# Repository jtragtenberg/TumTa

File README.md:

# TumTa - Instrumento Digital de Dança e Música voltado a disparar samples sonoros a partir de pisadas através de uma palmilha sensível à pressão (FSR).

## Descrição

**TumTa** é um sistema híbrido, modular e open-source, que integra:

- Hardware de detecção percussiva sensível ao toque.
- Firmware embarcado com processamento em tempo real.
- Comunicação sem fio via **XBee**.
- Software receptor/visualizador desenvolvido em **C++ com OpenFrameworks**.

O sistema foi desenvolvido para aplicações em:

- Performance musical ao vivo.
- Instalações audiovisuais interativas.
- Pesquisas em interfaces físico-digitais.

## Componentes do Projeto

### 1. Circuito eletrônico

- Projeto de circuito com sensores piezoelétricos.
- Arquivos disponíveis no repositório:
  - Esquema elétrico (.sch).
  - PCB para fabricação ou CNC (.brd).
  - Layout da caixa para **corte a laser** (.svg ou .dxf).

Todos os arquivos estão na pasta `hardware/`.

### 2. Firmware (Arduino)

- Processamento de sinais em tempo real com:
  - Derivada via diferenças finitas (float).
  - Controle **não bloqueante** com `millis()`.
  - Sistema de **debounce** ajustável.
  - Modos de envio: `DEBUG` e `LIVE`.

- Comunicação serial com módulo **XBee** para transmissão sem fio.
- Código modular e otimizado disponível na pasta `firmware/`.

### 3. Comunicação sem fio (XBee)

- Configuração clássica:
  - Transmissor: Arduino + XBee.
  - Receptor: XBee + computador.

- Baudrate: 38400.
- Comunicação robusta com protocolo de mensagem e **checksum**.

### 4. Software receptor (OpenFrameworks)

Desenvolvido em **C++ com OpenFrameworks**, o software realiza:

- Recepção e interpretação das mensagens enviadas via XBee.
- Detecção de picos ajustável, permitindo o controle da sensibilidade à intensidade.
- Mapeamento dinâmico: a intensidade controla diretamente a dinâmica dos samples gerados.
- Contorno de ruídos: filtros e thresholds ajustáveis para minimizar falsos disparos.
- Interface com `ofxGui` para ajuste em tempo real.
- Visualização gráfica dos dados recebidos.

**Integração MIDI**:

- O software converte os eventos de detecção percussiva em **mensagens MIDI**.
- Utiliza bibliotecas como `ofxMidi` para envio MIDI.
- As mensagens MIDI são enviadas em tempo real para uma **DAW** (ex.: **Ableton Live**, **Logic Pro**, **Reaper**).
- Cada batida detectada pode ser mapeada para **notas MIDI específicas**, disparando samples ou instrumentos virtuais.

## Fluxo geral do sistema

```
Sensor Piezo → Arduino → Processamento → XBee TX → ~~~ Wireless ~~~ → XBee RX → OpenFrameworks → MIDI OUT → DAW (Ableton Live)
```

## Arquivos incluídos no repositório

| Pasta            | Conteúdo                                                 |
|------------------|----------------------------------------------------------|
| `PCB/ Enclosure/ | Esquema, PCB (.brd/.sch), layout da caixa (.svg/.dxf).   |
| `Arduino/`       | Código Arduino (`TumTa.ino`).                            |
| `OpenFrameWorks/`| Projeto OpenFrameworks com envio MIDI.                   |
| `Imagens/`       | Fotos                                                    |
| `Max/`           | Software Aternativo                                      |

## Como montar o sistema

### 1. Hardware

- Construa o circuito com base no esquema elétrico.
- Corte a caixa com laser utilizando os arquivos vetoriais.
- Monte os componentes, conecte sensores, potenciômetro e switches.

### 2. Firmware

- Abra o `TumTa.ino` no Arduino IDE.
- Compile e envie para a placa Arduino.

### 3. Comunicação

- Configure os módulos **XBee**:
  - Mesma PAN ID.
  - Baudrate: 38400.
- Conecte o transmissor ao Arduino e o receptor ao computador.

### 4. Software

- Instale **OpenFrameworks** (versão 0.11 ou superior).
- Inclua `ofxMidi` para envio de mensagens MIDI.
- Abra o projeto `TumTa` na pasta `software/`.
- Ajuste:
  - Porta serial para XBee receptor.
  - Configurações MIDI (porta virtual ou física).
- Compile e execute.
- Configure a DAW (ex.: **Ableton Live**) para receber as mensagens MIDI provenientes do software.

## Parâmetros ajustáveis

| Parâmetro                | Local                            | Valor padrão |
|------------------------- |--------------------------------- |------------- |
| Threshold                | Potenciômetro (A7)               | Variável     |
| Debounce Time            | Estrutura `ChannelState`         | 150 ms       |
| Process Interval         | Global                           | 1 ms         |
| Tempo de Pisca (LED)     | Global                           | 500 ms       |
| Sensibilidade de Pico    | Interface do OpenFrameworks      | Ajustável    |
| Dinâmica de Sample/MIDI  | Mapeamento no software           | Ajustável    |
| Notas MIDI mapeadas      | Configuração no OpenFrameworks   | Ajustável    |

## Diferenciais do projeto

- Modular e expansível, com suporte para múltiplos sensores.
- Processamento híbrido, com divisão de carga entre hardware e software.
- Integração robusta com sistemas artísticos interativos e musicais.
- Arquivos completos: circuito, caixa e software.
- Envio de MIDI para **DAW** em tempo real.

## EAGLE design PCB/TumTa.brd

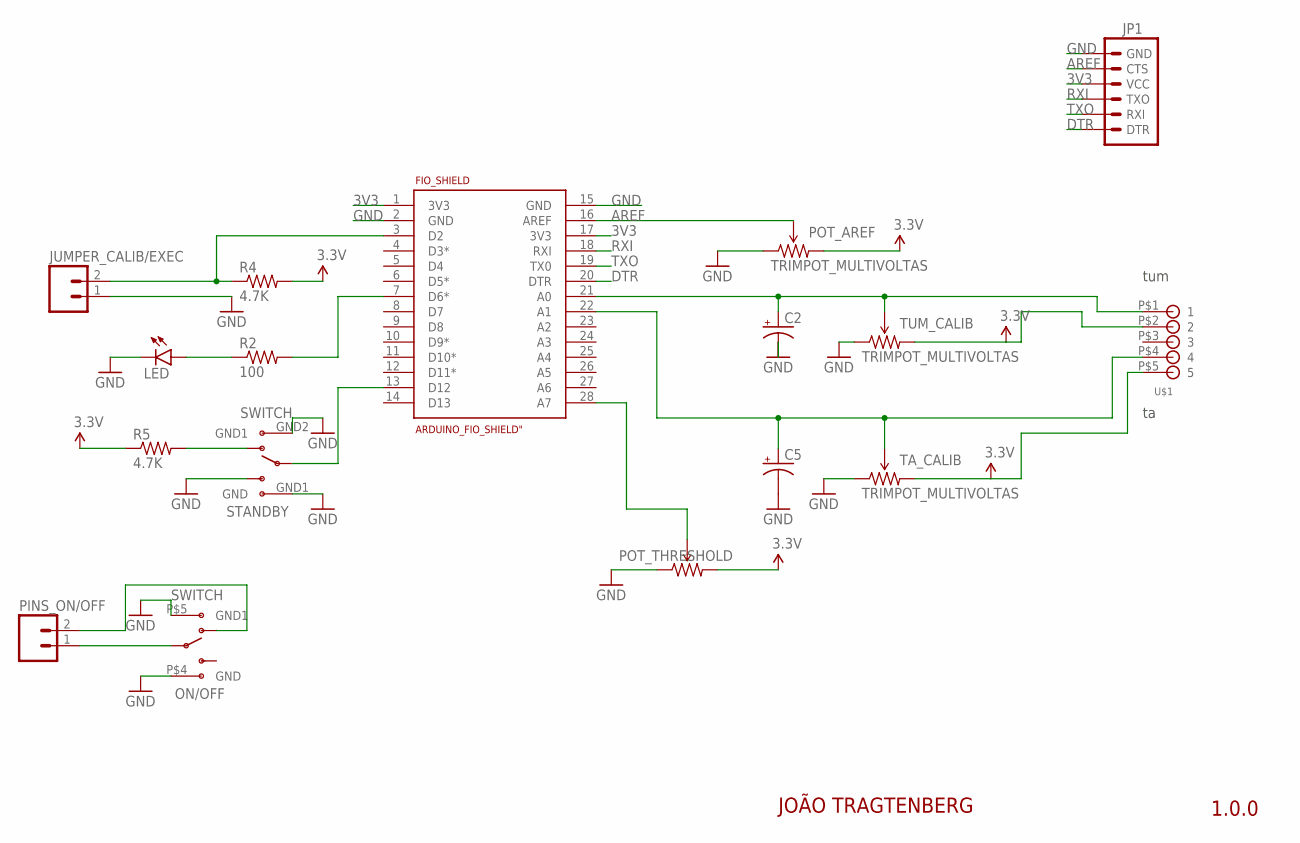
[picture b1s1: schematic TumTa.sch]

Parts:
C2, C5: CAP_POLPTH2; CPOL-RADIAL-10UF-25V
FIO_SHIELD: ARDUINO_FIO_SHIELD"; ARDUINO_FIO_SHIELD
JP1: ARDUINO_SERIAL_PROGRAMPTH; 1X06
JUMPER_CALIB/EXEC: M02PTH; 1X02
LED: LED-GREEN5MM_THRU; LED5MM
ON/OFF: SWITCH; SWITCH_HH_2POS_3PIN
PINS_ON/OFF: M02PTH; 1X02
POT_AREF: TRIMPOT_MULTIVOLTAS
POT_THRESHOLD: TRIMPOTBR; TRIM_POT_BR
R2: 100; 0603-RES
R4, R5: 4.7K; 0603-RES
STANDBY: SWITCH; SWITCH_HH_2POS_6PIN
TA_CALIB: TRIMPOT_MULTIVOLTAS
TUM_CALIB: TRIMPOT_MULTIVOLTAS
U$1: SCREWTERMINAL-5; SCREWTERMINAL-0.1"-5_BR

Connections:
3V3: FIO_SHIELD.1 (3V3), FIO_SHIELD.17 (3V3), JP1.4 (VCC), POT_AREF.3 (CW), POT_THRESHOLD.3 (CW), R4.2, R5.1, TA_CALIB.3 (CW), TUM_CALIB.3 (CW), U$1.P$2 (2), U$1.P$5 (5)
A0: C2.1 (+), FIO_SHIELD.21 (A0), TUM_CALIB.2 (WIPER), U$1.P$1 (1)
A1: C5.1 (+), FIO_SHIELD.22 (A1), TA_CALIB.2 (WIPER), U$1.P$4 (4)
AREF: FIO_SHIELD.16 (AREF), JP1.5 (CTS), POT_AREF.2 (WIPER)
D10: FIO_SHIELD.7 (D6*), R2.2
DTR: FIO_SHIELD.20 (DTR), JP1.1 (DTR)
GND: C2.2 (-), C5.2 (-), FIO_SHIELD.2 (GND), FIO_SHIELD.15 (GND), JP1.6 (GND), JUMPER_CALIB/EXEC.1, LED.K (C), ON/OFF.P$4 (GND), ON/OFF.P$5 (GND1), POT_AREF.1 (CCW), POT_THRESHOLD.1 (CCW), STANDBY.GND1 (GND), STANDBY.GND2 (GND1), STANDBY.P3A (S), TA_CALIB.1 (CCW), TUM_CALIB.1 (CCW)
unnamed: FIO_SHIELD.28 (A7), POT_THRESHOLD.2 (WIPER)
unnamed: FIO_SHIELD.3 (D2), JUMPER_CALIB/EXEC.2, R4.1
unnamed: FIO_SHIELD.13 (D12), STANDBY.P2A
unnamed: R5.2, STANDBY.P1A (O)
unnamed: ON/OFF.P$1 (O), PINS_ON/OFF.2
unnamed: LED.A, R2.1
unnamed: ON/OFF.P$2, PINS_ON/OFF.1
RXI: FIO_SHIELD.18 (RXI), JP1.3 (TXO)
TXO: FIO_SHIELD.19 (TX0), JP1.2 (RXI)

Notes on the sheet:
JOÃO TRAGTENBERG
1.0.0
tum

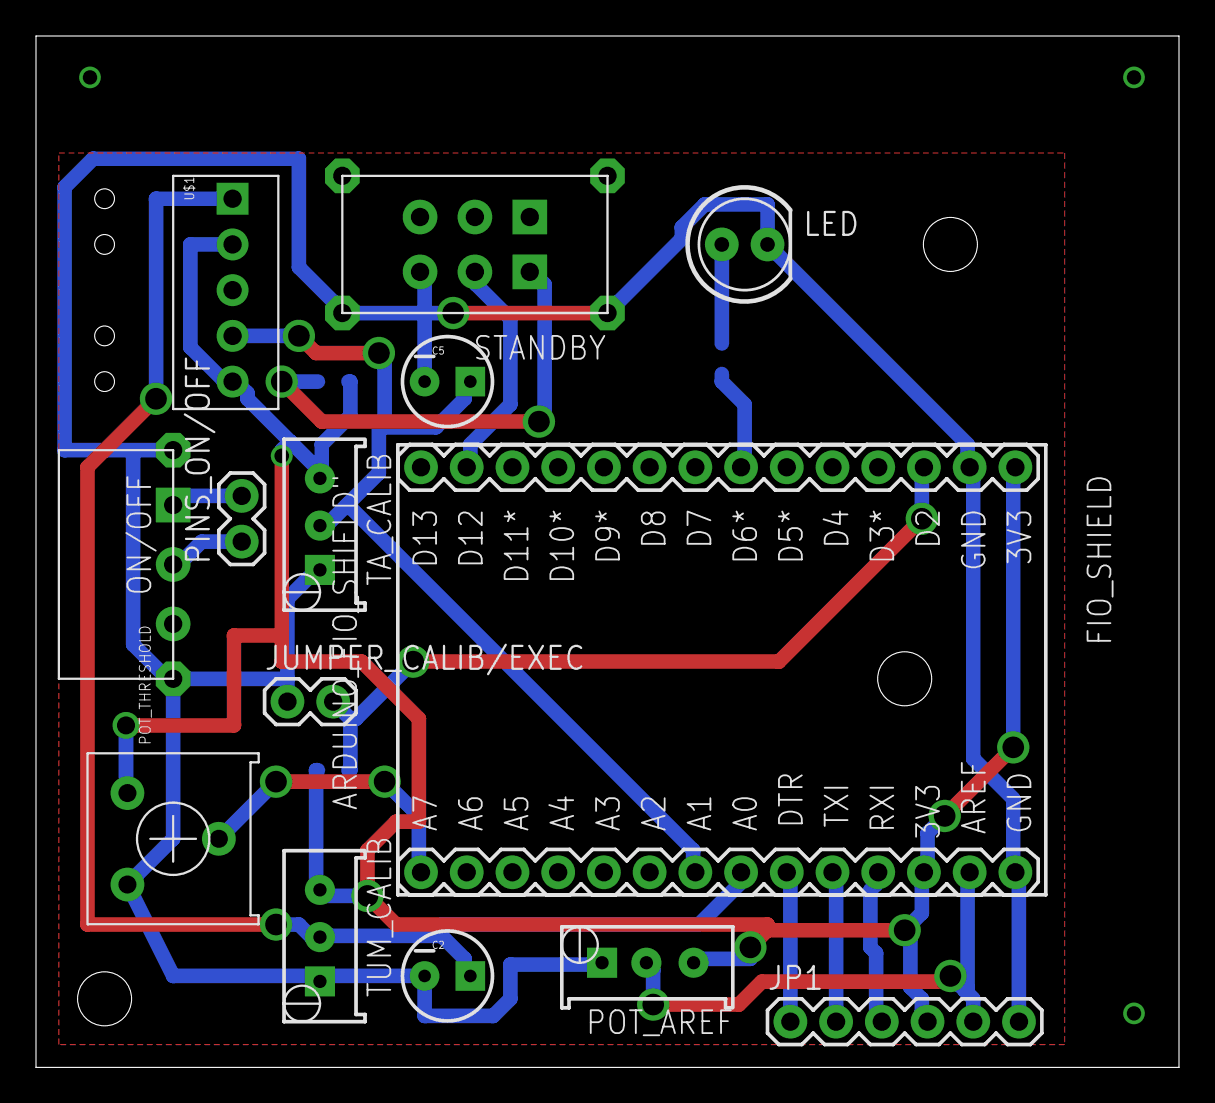
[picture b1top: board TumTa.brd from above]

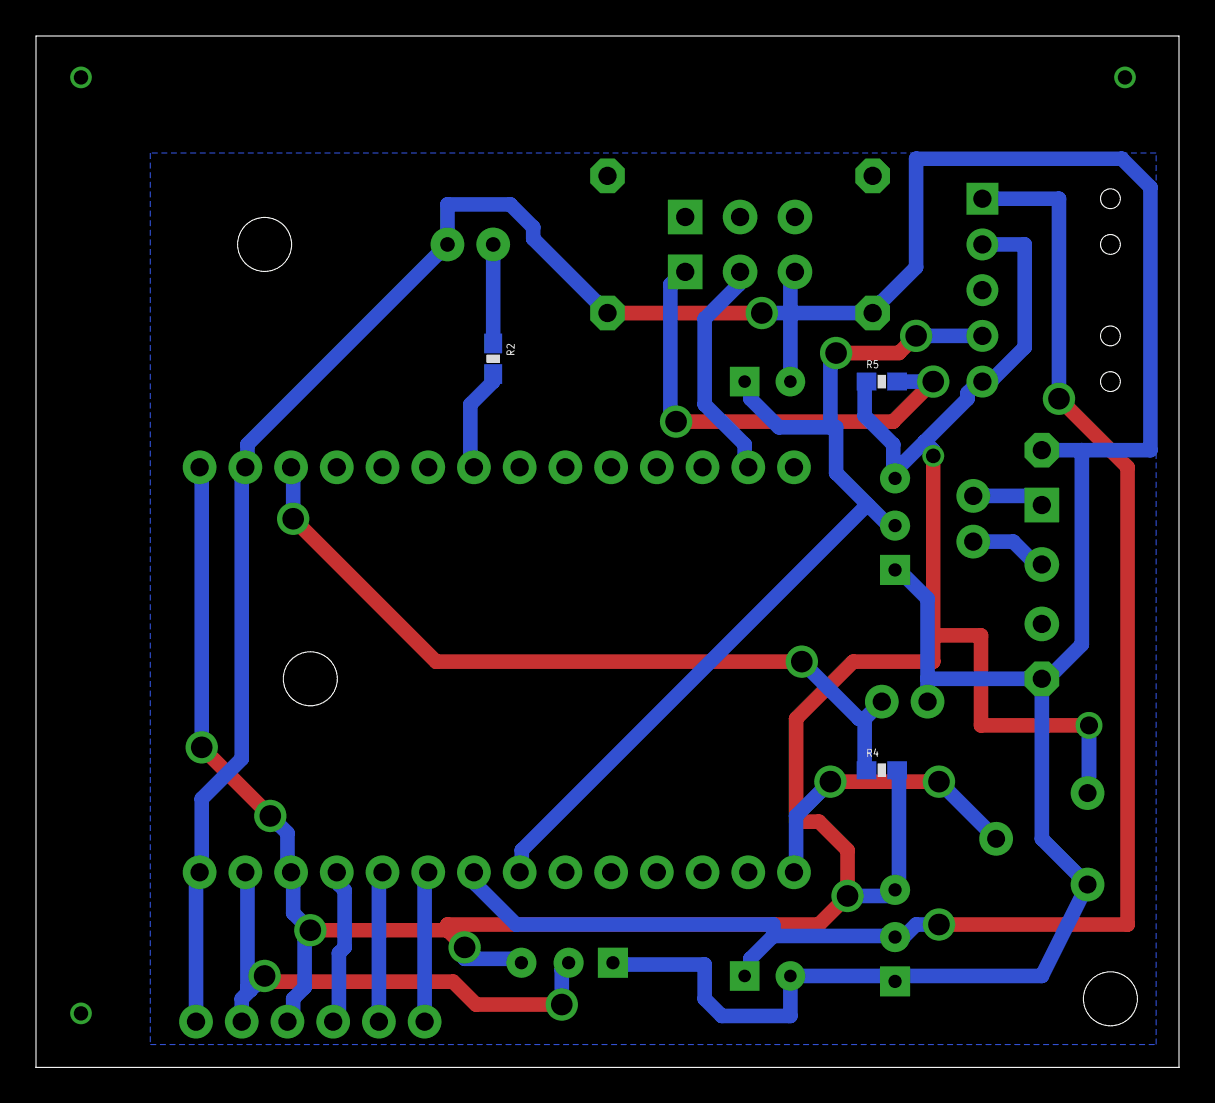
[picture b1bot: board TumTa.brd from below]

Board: 2 copper layers, 63.5 x 57.3 mm, 17 parts (3 on the bottom side), 16 nets.

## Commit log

2025-05-22 first tumta version
2025-05-22 gitignore
2025-05-22 v0_2_2
2025-05-22 v0_2_3
2025-05-22 v0_2_4
2025-05-22 v0_3_0
2025-05-22 v0_3_1
2025-05-22 v0_3_3
2025-05-22 v0_4_0
2025-05-22 caixa
2025-05-22 caixa melhorada
2025-05-22 adicionei texturas
2025-05-22 circuito v0_2_3
2025-05-22 v0_2_9
2025-05-22 v1_0_2
2025-05-22 v1_0_0
2025-05-22 v0_2_6
2025-05-22 v0_2_10
2025-05-22 v0_2_8
2025-05-22 v0_2_7
2025-05-22 v1_0_1
2025-05-22 v0_2_5
2025-05-22 added samples, live, openframeworks
2025-05-22 updated C++ Desktop Software
2025-05-22 added pcb image
2025-05-22 added abelton live sessions
2025-05-22 v2_0_0
2025-05-22 v1_0_4
2025-05-22 v1_0_3
2025-05-22 v2_0_2
2025-05-22 v2_1_1
2025-05-22 v1_1_0
2025-05-22 v2_2_2
2025-05-22 v2_2_1
2025-05-22 v2_1_2
2025-05-22 v2_0_3
2025-05-22 v2_2_2_Receiver
2025-05-22 v2_1_0
2025-05-22 v2_2_3
2025-05-22 v2_0_4 (n rolou)
2025-05-22 v2_2_3_Receiver
2025-05-22 v2_2_2_Receiver_DadosContinuos
2025-05-22 receiver e tumta
2025-05-22 C++ Openframeworks v5
2025-05-22 fotos
2025-05-22 C++ openframeworks update
2025-05-22 corrigi nome de arquivo
2025-05-22 voltei duas versões
2025-05-22 otimização e organização do fluxo do codigo
2025-05-22 mudança de delayMicrroseconds para non blocking strategy
2025-05-22 erro no commit anterior

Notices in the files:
parts and their libraries:
SparkFun-Electromechanical: Licensing: Creative Commons ShareAlike 4.0 International - https://creativecommons.org/licenses/by-sa/4.0
